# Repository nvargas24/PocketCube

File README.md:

# PocketCube
Proyecto satelital desarrollado por el grupo de investigación **SyCE** (Simulación y Cálculo de Campos Electromagnéticos).

## Funcionamiento de la Aplicación
La aplicación se encarga de monitorear las lecturas provenientes de un **1 pin de entrada** habilitados en la *Carga Útil*.

### Características de la Aplicación

- **Selección de puerto serie**: Se identifican los dispositivos conectados al ordenador, el usuario debe seleccionar el correspondiente al Arduino UNO (Pocket Main).
  *ACLARACIÓN:* Seleccionar CH340 , arduino chino conectado actualmente en el poncho.

- **Menu de configuración**: Menu interactivo para usuario realizar la configuraciones necesarias para determinar el procesaimentos de lo datos a visualizar.
- **Display DateTime**: Se cuenta con 2 display para mostrar tiempos
  - **Display 1**: Muestra el horario actual registrada por PocketMain.
  - **Display 2**: Muestra la fecha actual registrada por PocketMain.
- **Ventana de monitoreo de pulsos**: Permite visualizar las mediciones solicitadas y realizadas por la *Carga Útil*. En esta ventana se cuentan con:
  - **Grafico de barras**: Muestra los pulsos detectados por la *Carga Útil*, limitado por el intervalo de tiempo asignado por el usuario.
  - **Tabla contador de pulsos**: Muestra el registro de datos ordenados a medida que el *Pocket Main* reciba datos (ver sección [Procesamiento de datos](#procesamiento-de-datos))
  - **Barra de progreso**: Barra de carga que indica cuando se cumple el intervalo de tiempo asignado.
- **Ventana de calculo de CPS**: Permite visualizar el promedio obtenido en cada intervalo de tiempo (CPS).
  - **Grafico de lineas**: Muestra el avance de los CPS obtenidos en cada intervalo.
  - **Tabla contador de pulsos**: Muestra el registro de los calculos obtenidos para cada intervalo.
- **Indicador de estado**: en forma simple el Arduino puede indicar algun estado en particular
  - **Read EEPROM**: Lectura de memoria EEPROM
  - **Clear EEPROM**: Vacio de memoria EEPROM
  - **Read MEAS**: Lectura de datos matcheados con RTC
  - **Error**: Estado particular cuando no se reonoce ID
- **Opciones de usuario**: Botones para interactuar con la aplicación.
  - **Ver Data Serial**: Visualiza en un tabal todos los datos recibidos, no procesados, por la aplicación.**[No disponible]**
  - **Exportar CSV**: Crea 2 archivos .csv , cada uno todos los datos registrados en la tablas de ambas ventanas de datos.
  - **Formulas**: **[No disponible]**
  - **Salir**: Cierra la aplicación y todos los procesos relacionados.

## Pocket Main
El Arduino conectado con el poncho de módulos se lo considera el *Pocket Main*. 

**ACLARACIÓN:**: Actualmente tiene cargado el programa para funcionar con la otro Arduino UNO como *Carga Útil*.

### Comunicación I2C con la Carga Útil
Se utiliza el protocolo **I2C** para la comunicación entre el **Arduino UNO** (Pocket Main) y la **Carga Útil** (Arduino UNO o ATtiny85).

| Pin ATtiny85 | Pin Arduino UNO   | Pin PocketMain | Función  |
|--------------|-------------------|----------------|----------|
| PB0          | A4                | A4             | SDA      |
| PB2          | A5                | A5             | SCL/SCK  |
| GND          | GND               | GND            | GND      |

### Procesamiento de datos
El **Arduino UNO** es responsable de recibir, procesar y enviar los datos provenientes de la Carga Útil a la aplicación.
Los datos se muestran en uno de los siguientes formatos para optimizar tramas de datos:
  - **Formato simple**: `{ID},{value}`
  - **Formato extendido**: `{ID},{datetime} {value}`

  ### Asignación de IDs
  Para simplificar la identificación de los diferentes datos, se han asignado los siguientes **ID**:

  | ID    | Descripción     |
  |-------|-----------------|
  | 1     | MEAS1           |
  | 2     | MEAS2           |
  | 3     | RTC             |
  | 4     | EEPROM_USED     |
  | 5     | EEPROM_DATA     |
  | 6     | STATE           |

  Estos formatos permiten identificar fácilmente el origen de los datos (`ID`) y el valor asociado (`value`). En el formato extendido, se incluye además información adicional como la marca de tiempo (`datetime`) y un valor (`value`).
  
## Carga Útil
### Con Attiny85
La Carga Útil opera en modo de conteo de pulso por PCINT: **Modo ISR** (PB3 Habilitado).

| Pin ATtiny85 | Tipo de pin   | Modo de operación | Función  |
|--------------|---------------|-------------------|----------|
| PB3          | PCINT3        | CHANGE            | MEAS1    |
| PB4          | PCINT4        | CHANGE            | MEAS2    |

- **Aclaración**: El Attiny por su limitaciones de pines, no se puede usar en simultaneo el uso de Interrupciones y el I2C, debido a que utilizan el mismo pin para los pulsos de clock (SCL), como alternativa cuenta con pines PCINT que son similares a las interrupciones pero no son configurables el metodo de detección de pulsos, solo admite por CHANGE. Tambien tener en cuenta que al no ser con las ISR no son precisos y presentan otra complicaciones.

Para cargar programas (Debuggear) al ATtiny85 con el Arduino UNO, ver sección [Depuración y Carga de Programas en el ATtiny85](#Depuración-y-Carga-de-Programas-en-el-ATtiny85)

#### Esquemáticos de Conexión

#### Montaje de Poncho

### Con Arduino UNO
Opera contando pulsos por ISR, interupciones por Hardware. A diferencia de los PCINT son mas precisos: **Modo ISR** (Pin 2 Habilitado).

| Pin Arduino  | Tipo de pin   | Modo de operación | Función  |
|--------------|---------------|-------------------|----------|
| Pin2         | INT0          | RISING            | MEAS1    |
| Pin3         | INT1          | RISING            | MEAS2    |

#### Esquemáticos de Conexión

#### Montaje de Pocket Main con Carga Útil

## Ejemplos de uso
### Con Arduino UNO
#### Pasos previos
1. Asegurarse de tener conectados todos ambas placas de desarrollo como se indica en el esquematico. En caso de *Pocket Main* la conexión ya esta realiza en el poncho.
2. Cargar programa en Arduino UNO referido como *PocketMain* ( [Programa_PocketMain](Carga_util/pocket_slave/pocket_main.ino) )
3. Cargar programa en Arduino UNO referido como *Carga Útil* ( [Programa_Carga_Útil](Carga_util/pocket_slave/pocket_slave.ino) )
4. Conectar *PocketMain* a PC, y *Carga Útil* a la alimentación del *Pocket Main* o tambien puede ser alimentado por una fuente externa: PC o fuente de 5VDC.
5. Asegurarse que la PC reconce los Arduinos, principalmete si se opera con un Arduino chino. Si alguno de los Arduino es chino instalar: 
[URL_Arduino_chino](https://www.arduined.eu/ch340-windows-10-driver-download/). Verificarlo en *Adminitrador de dispositivos*.

Una vez finalizados los *Pasos previos*, acceder a la aplicación de escritorio.

1. Al iniciar la aplicación detectara loos dispositivos conectados en los puertos. Seleccionar: **USB-SERIAL CH340** (si tiene como *PocketMain* el Arduino chino).

2. Una vez seleccionado el dispositivo, ingresar el intervalo de tiempo para cada ventana de tiempo.

3. Con esto configurado, click en *Iniciar* y empezara a correr el programa.

El *Pocket Main* empezara a solicitar lecturas realizadas a la *Carga Útil* cada **1 segundo** esto controlado por un TIMER interno. Estas lecturas son indentificadas por la aplicación, procesadas y presentadas tanto en el gráfico de barras como en la tabla. La duración de cada proceso dependera del intervalo de tiempo asignado por el usuario, el cual se podrá ver su progreso en una barra de carga.

Al finalizar cada intervalo de tiempo, la aplicación procesa estos datos, obteniendo el promedio de estos (CPS). Estos podrán tambien visualizarse en el gráfico de lineas y en la tabla continua.

Todos estos datos son visualizados en tiempo real, pero tambien registrados en un Dataframe el cual cuando el usuario lo solicite pueden exportarse como archivos CSV. 

## Pinouts de microcontroladores
### Arduino Uno

El **Arduino Uno** utiliza los siguientes pines para la comunicación I2C:

Estos pines están conectados internamente al módulo TWI (Two Wire Interface) del microcontrolador.

### ATtiny85

El **ATtiny85** utiliza los siguientes pines:

## Depuración y Carga de Programas en el ATtiny85

Para cargar un programa en el **ATtiny85** utilizando un **Arduino UNO** como programador, sigue estos pasos. Es necesario conectar los pines de depuración (Debugger) de acuerdo a la interfaz SPI.

### Conexión de Pines SPI (Debugger)

Conecta los pines del **Arduino UNO** a los del **ATtiny85** de la siguiente manera:

| Pin Poncho ATtiny85 | Pin Arduino UNO   | Función  |      Descripción    |
|---------------------|-------------------|----------|---------------------|
| 1                   | 10                | SS       | Slave Select        |
| 2                   | 11                | MOSI     | Master Out Slave In |
| 3                   | 12                | MISO     | Master In Slave Out |
| 4                   | 13                | SCK      | Serial Clock        |

- **SS (Slave Select):** Pin 1 (Móodulo ATtiny85)
- **MOSI (Master Out Slave In):** Pin 2 (Módulo ATtiny85)
- **MISO (Master In Slave Out):** Pin 3 (Módulo ATtiny85)
- **SCK (Serial Clock):** Pin 4 (Módulo ATtiny85)

### Carga del Programa "ArduinoISP"

Una vez realizada la conexión de los pines, sigue estos pasos:

1. En el IDE de Arduino, ve a **Ejemplos -> ArduinoISP -> ArduinoISP.ino**.
2. Carga este programa en tu **Arduino UNO**.

### Instalación de la Librería para el ATtiny85

Antes de cargar cualquier programa en el **ATtiny85**, asegúrate de que el IDE de Arduino tenga instalada la librería necesaria para reconocer el microcontrolador.

1. Ve a **Preferencias** en el IDE de Arduino.
2. En el campo **Gestor de URLs Adicionales de Tarjetas**, añade la siguiente URL:
https://mcudude.github.io/MiniCore/package_MCUdude_MiniCore_index.json
https://raw.githubusercontent.com/damellis/attiny/ide-1.6.x-boards-manager/package_damellis_attiny_index.json
3. Descargar libreria TinyWireS: 
https://playground.arduino.cc/uploads/Code/TinyWireS/index.zip
4. Descomprimir el .zip y agregar a la carpeta ***libraries*** de Arduino
5. Finalmente resetear IDE Arduino para guardar configuraciones

### Configuración en el IDE de Arduino

Una vez que la librería esté instalada, configura el IDE de Arduino de la siguiente manera:

- **Placa:** ATtiny25/45/85
- **Clock:** Internal 1MHz
- **Proccessor:** ATtiny85
- **Port:** [Selecciona el puerto correspondiente al Arduino UNO]
- **Programador:** Arduino as ISP

### Carga de programas en el ATtiny85

Con la configuración correcta y el **Arduino UNO** programado como ISP, ya puedes cargar un programa en el **ATtiny85** de la misma manera que lo harías en un Arduino UNO. Solo asegúrate de seleccionar el **programador** correcto antes de realizar la carga.

## Referencias

Para más información, consulta la documentación oficial de [attitny85](https://www.microchip.com/en-us/product/attiny85) y [Arduino Uno](https://www.arduino.cc/en/Main/ArduinoBoardUno).

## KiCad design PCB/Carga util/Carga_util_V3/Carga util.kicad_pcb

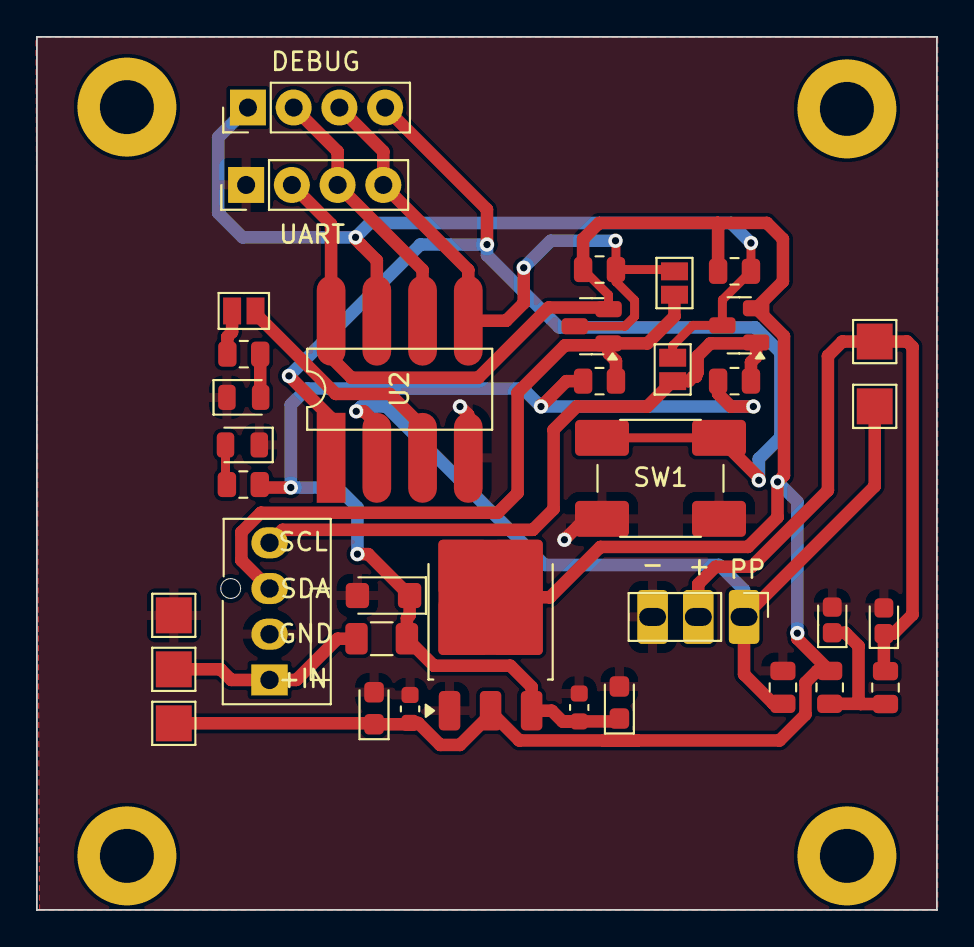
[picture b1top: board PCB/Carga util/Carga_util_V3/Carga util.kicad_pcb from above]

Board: 2 copper layers, 50.0 x 48.5 mm, 36 parts (0 on the bottom side), 17 nets.

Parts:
+3.3V: Test_+3.3V; TestPoint_Pad_2.0x2.0mm
C1, C4: 10uF; CP_EIA-2012-15_AVX-P
C2, C3: 100nF; C_0603_1608Metric
C5: 4.7u; CP_EIA-1608-08_AVX-J
C6: 4.7uF; CP_EIA-1608-08_AVX-J
D1: D_Shockley; D_SMF
D2: PW; LED_0805_2012Metric
D3: Test; LED_0805_2012Metric
F1: Fuse_Small; Fuse_1206_3216Metric
GND: Test_GND; TestPoint_Pad_2.0x2.0mm
IN: Test_+3.7V; TestPoint_Pad_2.0x2.0mm
J1: UART; PinHeader_1x04_P2.54mm_Vertical
J2: CONN; FanPinHeader_1x04_P2.54mm_Vertical
J3: DEBUG; PinHeader_1x04_P2.54mm_Vertical
J4: BG51; PinHeader_1x03_P2.54mm_Vertical
JP1, JP2, JP3: SolderJumper_2_Open; SolderJumper-2_P1.3mm_Open_Pad1.0x1.5mm
PP: Test_PP; TestPoint_Pad_2.0x2.0mm
Q1, Q2: NMOS; SOT-23
R1, R7: 220; R_0805_2012Metric
R2, R3: 1.8k; R_0805_2012Metric
R5, R6, R8, R9, R10: 10k; R_0805_2012Metric
SW1: Reset; SW_PUSH_6mm
U1: LM1117DT-3.3; TO-252-3_TabPin2
U2: ATtiny85-20S; DIP-8_W7.62mm_LongPads
VCCF: Test_VCC_Filter; TestPoint_Pad_2.0x2.0mm

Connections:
+3.3V: +3.3V.1, C1.1, C2.1, J1.2, Q1.2 (G), Q2.2 (G), R2.1, R5.1, R8.1, U1.2 (VO), U2.8 (VCC)
+3.7V: C3.1, C4.1, D1.1 (K), F1.1, R1.1, R6.1, R9.1, U1.3 (VI)
/DI: J1.4, J3.3, JP2.1 (A), Q1.3 (S), R5.2, U2.5 (AREF/PB0)
/DO: J1.3, J3.2, U2.6 (PB1)
/IN: F1.2, IN.1, J2.1
/PP: J4.1, PP.1, R10.1, U2.2 (XTAL1/PB3)
/SCK: J3.1, JP3.1 (A), Q2.3 (S), R8.2, U2.7 (PB2)
/SCL_HV: J2.4, JP3.2 (B), Q2.1 (D), R9.2
/SDA_HV: J2.3, JP2.2 (B), Q1.1 (D), R6.2
/SS: J3.4, SW1.1, U2.1 (~RESET/PB5)
/VDC_Filter: C6.1, J4.2, R3.2, VCCF.1
GND: C1.2, C2.2, C3.2, C4.2, C5.2, C6.2, D1.2 (A), D2.1 (K), D3.1 (K), GND.1, J1.1, J2.2, J4.3, R10.2, SW1.2, U1.1 (GND), U2.4 (GND)
unnamed: C5.1, R2.2, R3.1
unnamed: D2.2 (A), R1.2
unnamed: D3.2 (A), R7.2
unnamed: JP1.1 (A), R7.1
unnamed: JP1.2 (B), U2.3 (XTAL2/PB4)

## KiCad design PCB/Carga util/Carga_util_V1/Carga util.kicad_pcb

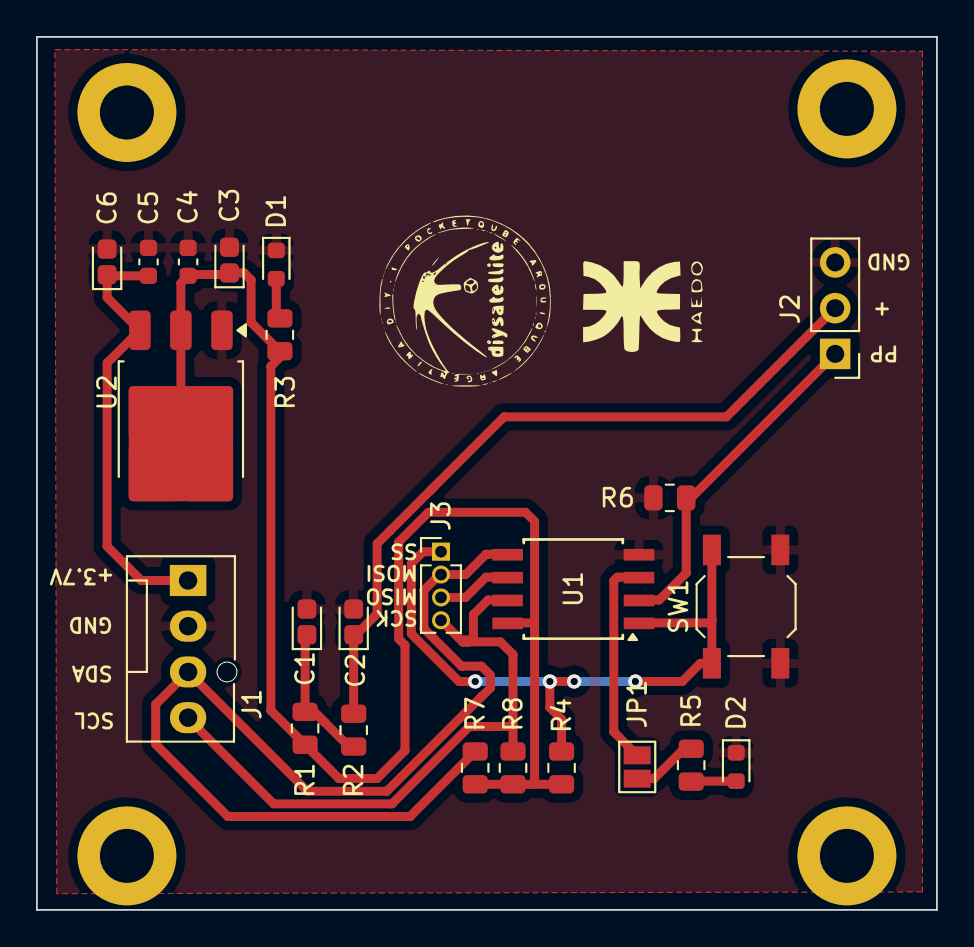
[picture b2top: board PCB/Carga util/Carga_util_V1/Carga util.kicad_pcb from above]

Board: 2 copper layers, 50.0 x 48.5 mm, 23 parts (0 on the bottom side), 14 nets.

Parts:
C1, C2: 4.7u; CP_EIA-1608-08_AVX-J
C3, C6: 10uF; CP_EIA-1608-08_AVX-J
C4, C5: 100nF; C_0603_1608Metric
D1: PW; LED_0603_1608Metric
D2: Test; LED_0603_1608Metric
J1: CONN; FanPinHeader_1x04_P2.54mm_Vertical
J2: BG51; PinHeader_1x03_P2.54mm_Vertical
J3: DEBUG; PinHeader_1x04_P1.27mm_Vertical
JP1: SolderJumper_2_Open; SolderJumper-2_P1.3mm_Open_Pad1.0x1.5mm
R1, R2: 1.8k; R_0805_2012Metric
R3, R5: 220; R_0805_2012Metric
R4, R7, R8: 4.7k; R_0805_2012Metric
R6: 10k; R_0805_2012Metric
SW1: Reset; SW_SPST_TL3342
U1: ATtiny85-20S; SOIC-8W_5.3x5.3mm_P1.27mm
U2: LM1117DT-3.3; TO-252-3_TabPin2

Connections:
+5V: C5.1, C6.1, J1.1, U2.3 (VI)
/MISO: J3.3, U1.6 (PB1)
/MOSI: J1.3, J3.2, R7.2, U1.5 (AREF/PB0)
/PP: J2.1, R6.1, U1.2 (XTAL1/PB3)
/SCK: J1.4, J3.4, R8.2, U1.7 (PB2)
/SS: J3.1, R4.2, SW1.1, U1.1 (~RESET/PB5)
GND: C1.2, C2.2, C3.2, C4.2, C5.2, C6.2, D1.1 (K), D2.1 (K), J1.2, J2.3, R6.2, SW1.2, U1.4 (GND), U2.1 (GND)
unnamed: C1.1, R1.2, R2.1
unnamed: D1.2 (A), R3.2
unnamed: D2.2 (A), R5.2
unnamed: C2.1, J2.2, R2.2
unnamed: JP1.1 (A), R5.1
unnamed: JP1.2 (B), U1.3 (XTAL2/PB4)
VCC: C3.1, C4.1, R1.1, R3.1, R4.1, R7.1, R8.1, U1.8 (VCC), U2.2 (VO)

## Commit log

2024-07-30 version original funcional - sin correcciones
2024-07-30 Borro comentarios no relevantes y ordeno heard
2024-08-01 cargo gitignore
2024-08-03 ejemplo RTC con arduino-ESP32
2024-08-03 ejemplo master-slave i2c, falta test
2024-08-03 simulacion LTC3105
2024-08-03 Pinout de placas de desarrollo
2024-08-03 update readme, solo pinout
2024-08-04 test de comunicacion i2c ok
2024-08-07 sincronizo RTC de master-slave, falta rta de slave
2024-08-07 envio de str , rta de slave-master
2024-08-07 add response de slave con concat
2024-08-07 rta from slave con datos propios
2024-08-08 sicro ok, limite de 33 char
2024-08-12 simul celdas solares
2024-08-15 paso a SPI por buffer - falta test
2024-08-22 test spi ok, falta rta dataset de slave a master
2024-08-22 rta de slave cortado, add 2da solicitud master
2024-08-24 app simulador de carga util
2024-08-25 add grafico dinamico- falta ver grilla
2024-08-25 add grilla dinamica
2024-08-25 indicador de data a enviar y timer
2024-08-27 ajusto dimensiones de graficos
2024-08-27 restauro a version de i2c
2024-08-27 ordeno y comento cod master
2024-08-27 ordenamiento de cod slave
2024-08-27 ajuste de dimensiones de ventana y widgets
2024-08-27 estructuro envio de datos serial pc a master_esp32
2024-08-29 habilito DAC
2024-08-29 modifico ubicacion de widgets
2024-08-29 agrego lectura de puerto serial - falta test
2024-08-29 ignoro archivos .doc y .ppt
2024-09-01 comunicacion serial e i2c entre app y dispositivos
2024-09-01 estandarizo id y muestro datos de dispo. en app
2024-09-01 arreglo problema msj que no cumplen formato de cmd
2024-09-01 creo funcion para formato de cmd
2024-09-02 agrego timer - un poco lento
2024-09-03 window y add dac2 a medias
2024-09-07 organizo codigo de app- ver falla de qtime
2024-09-07 reduzco los delay para mejor lectura de datos por i2c
2024-09-07 imagenes de arduino
2024-09-08 aumento velocidad de envio de datos por uart
2024-09-09 optimizo cod master arduino
2024-09-09 funcion para formato a enviar datos
2024-09-12 cambio de esp32 a arduino unno chino
2024-09-15 confgi arduinos para 2 mediciones
2024-09-15 modifico ui para mediciones pseudo realtime
2024-09-15 Muestro valor y tiempo en segundos de slave
2024-09-16 guardo y leo datos de eeprom generico - revisar
2024-09-22 elimino carcateres innecesarios
2024-09-22 concateno envio de los datos de mediciones a app
2024-09-22 cambbio variable global a local por memoria
2024-09-22 ordeno lectura de eeprom para enviar archivo
2024-09-22 funcion para enviar lectura de eeprom a app
2024-09-26 adapto para procesar 2 mediciones en una trama
2024-09-26 muestro state en app
2024-09-26 modifico posicion de widgets
2024-09-26 mod name macros
2024-09-29 borro timer de slave y muestro datos por consola
2024-09-29 creo func para carga a csv
2024-09-30 optimizo cod arduino para save data eeprom
2024-10-09 cargo pinout de attiny85
2024-10-09 cargo devuelta pinout attiny85
2024-10-16 cargo sch y pcb de diseño de ponchos
2024-10-16 img de app
2024-10-16 cargo cod original de bg51 para detectar pulsos
2024-10-16 diagramas en bloques de ejemplo bg51
2024-10-21 cargo datasheets
2024-10-21 datasheet de attiny85
2024-10-26 cargo appv2 para test de bg51
2024-10-26 update md
2024-10-26 ajusto para recibir datos solo de master
2024-10-26 cargo ejemplo de i2c attiny-arduino
2024-10-28 modifico archivos para implementar PCINT con attiny
2024-10-31 add control de i2c por timer de user cada 1 seg
2024-10-31 intento logica para enviar datos solo cuando hay cambios
2024-11-04 mod format data para ver en ui
2024-11-05 obtengo configuracion de usuario
2024-11-09 carga de datos en tablas con formato adecuado
2024-11-11 adapto grafico de cp segun intervalo time
2024-11-11 habilito grafico de dosis - ver grilla y
2024-11-11 ajustes de presentacion de graficos y widgets
2024-11-11 habilito progressbar de contador de pulsos
2024-11-12 carga en df y exportacion a csv
2024-11-12 add identifiacion de intervalo en df countpulse
2024-11-12 corrijo error en asignacion de df temporales
2024-11-12 load programa de attiny en arduino aux por problema de i2c attiny
2024-11-14 ajusto dimensiones de app
2024-11-14 add ventana para ver datos seriales
2024-12-23 test de read rtd, lee pero no el valor real como con rtclib
2025-04-23 Actualizar documentación en README.md
2025-04-23 comento codigo de rtc, para que no tilde arduino, attiny85 no responde
2025-04-24 Borro no relevante en pocket - dejando solo uart, i2c e INT
2025-04-24 Borro codigo irrelevante n attiny8, solo dejo i2c y pcint lectura
2025-05-15 Remove commented-out code and improve logging in I2C and UART communication
2025-06-09 Refactor code structure for improved readability and maintainability - PCB Kicad
2025-06-09 Refactor code structure for improved readability and maintainability
2025-06-09 Update .gitignore to include additional temporary, log, and output files
2025-07-22 Add lock files for autosave of schematic and PCB with user details
2025-07-26 Correccion de formato de carga de datos a app y borro print auxiliares
2025-07-28 update v2 interfaz ui
2025-07-28 add lectura datetime de pc
2025-07-28 arreglo formato de lectura parea calculo de cps
2025-07-28 modifico ui - ver tiempo de ensayo
2025-07-29 update ui
2025-07-29 add interval test y borro code innecesario
2025-07-29 update para tabla cps
2025-07-29 add durancion de test
2025-07-29 add clear para nuevo ensayo
2025-08-15 add: nuevo readme de nueva version de app y pcb poncho
2025-09-09 refactor: forma de exporta csv con pathlib
2025-09-09 nuevo pcb
2025-09-25 update pcb para pocket
2025-09-25 update 2 pcb pocket
2025-10-26 add: txt con librerias requeridas
2025-10-26 update: cambio a pyside6
2025-10-26 update: ui a pyside6
2025-11-05 filter: librerias dedicas a ser utilizadas en la app con qt
2025-11-05 update: maximizo espacio canvas de graficos measure
2026-01-13 update: vista app para sniffer only
2026-01-13 add: modulo para utilizar en otro programa de contador bg51
2026-01-13 update: requirement para entorno virtual de app
2026-01-15 update: simplifico codigo autonomo para libreria que usa arduino
2026-01-15 update: comentarios en attiny
2026-01-15 update: add comment to clarify I2C command reception in loop
2026-01-19 add: url para usar attiny85 en ide arduino
2026-01-20 add: nueva version de test por comandos y attiny rta cada 1 min
2026-01-20 remove: optimizacion de variables y funciones no utilizadas
2026-01-21 update: optimizo codigo test para usar por comando solicitudes al attiny
2026-01-21 update: nuevos comandos para independizar attiny, solo responde solicitado al arduino
2026-01-21 add: creo modulos para test mas ligero y facil de comprender
2026-01-21 add: ui para testear comandos y rtas de attiny por uart
2026-01-21 add: new app para utilizar comandos uart directamente por medio del arduino
2026-01-23 update: nombre de widgets
2026-01-23 update: colores resaltantes para el texto
2026-01-23 add: try-except para deteccion de puertos
2026-01-23 refactor: actualizacion de timer pc en ms y deteccion de btn select para enviar cmd a arduino
2026-01-23 add: identifico metodos, variables y constantes
2026-01-23 add: temporizador
2026-01-23 update: habilito consultas a attiny desde app por uart-uart-i2c
2026-01-23 refactor: disminuyo delay para mejor respuesta - aun es un poco lento
2026-01-23 update: labels de graficos matplotlib
2026-01-24 refactor: instancias para des/habilitar widgets
2026-01-26 update: estructuro datos para consultas manuales y por ensayo con IDs
2026-01-26 update: segmentacion de datos para widgets - falta adecuar tiempos de uart
2026-01-26 add: timeout de serial a 3 seg
2026-01-26 add: diferenciacion de datos long como CPS+TIME
2026-01-26 refactor: cambio de poling a ISR el contador de seg en ATTiny
2026-01-27 refactor: estilo win11 para widgets
2026-01-27 update: optimizo para consulta mas rapidas y respuestas sin delay por uart
2026-01-27 refactor: agrego lineas auxiliares a grafico de lineas
2026-01-27 update: mejoro perfomance de grafico de lineas
2026-01-28 add: contador 1min con count1s
2026-01-28 add: lectura de puertos auto cada 3seg
2026-01-28 add: lectura de puerto COM si cerrar app
2026-01-28 refactor: apertura y cierre de puerto en pseudo tiempo real
2026-01-29 refactor: uso de manual y auto ok- falta continuidad luego de primer ensayo volver a usar el modo manual
2026-01-29 refactor: solucionado continuidad entre modo manual y auto, falta ver reseteo de algunas variables
2026-01-29 refactor: add reset de contadores cuando se recibe un dato en modo auto para tablas
2026-01-29 refactor: tiempo para consulta cpm y timeout
2026-01-29 add: crear archivos csv y modificacion de perfomance CPM. ver inicio que hay error de waiting y caambiar "," por ";" en cvs
2026-01-29 refactor: logica de usb conectado y desconectado
2026-01-29 refactor: instacias para habilitar exportar
2026-01-30 add: documento funcionamiento de APP, ATtiny y y libreria para Pocket
2026-01-30 update: redaccion de readme para appv3
